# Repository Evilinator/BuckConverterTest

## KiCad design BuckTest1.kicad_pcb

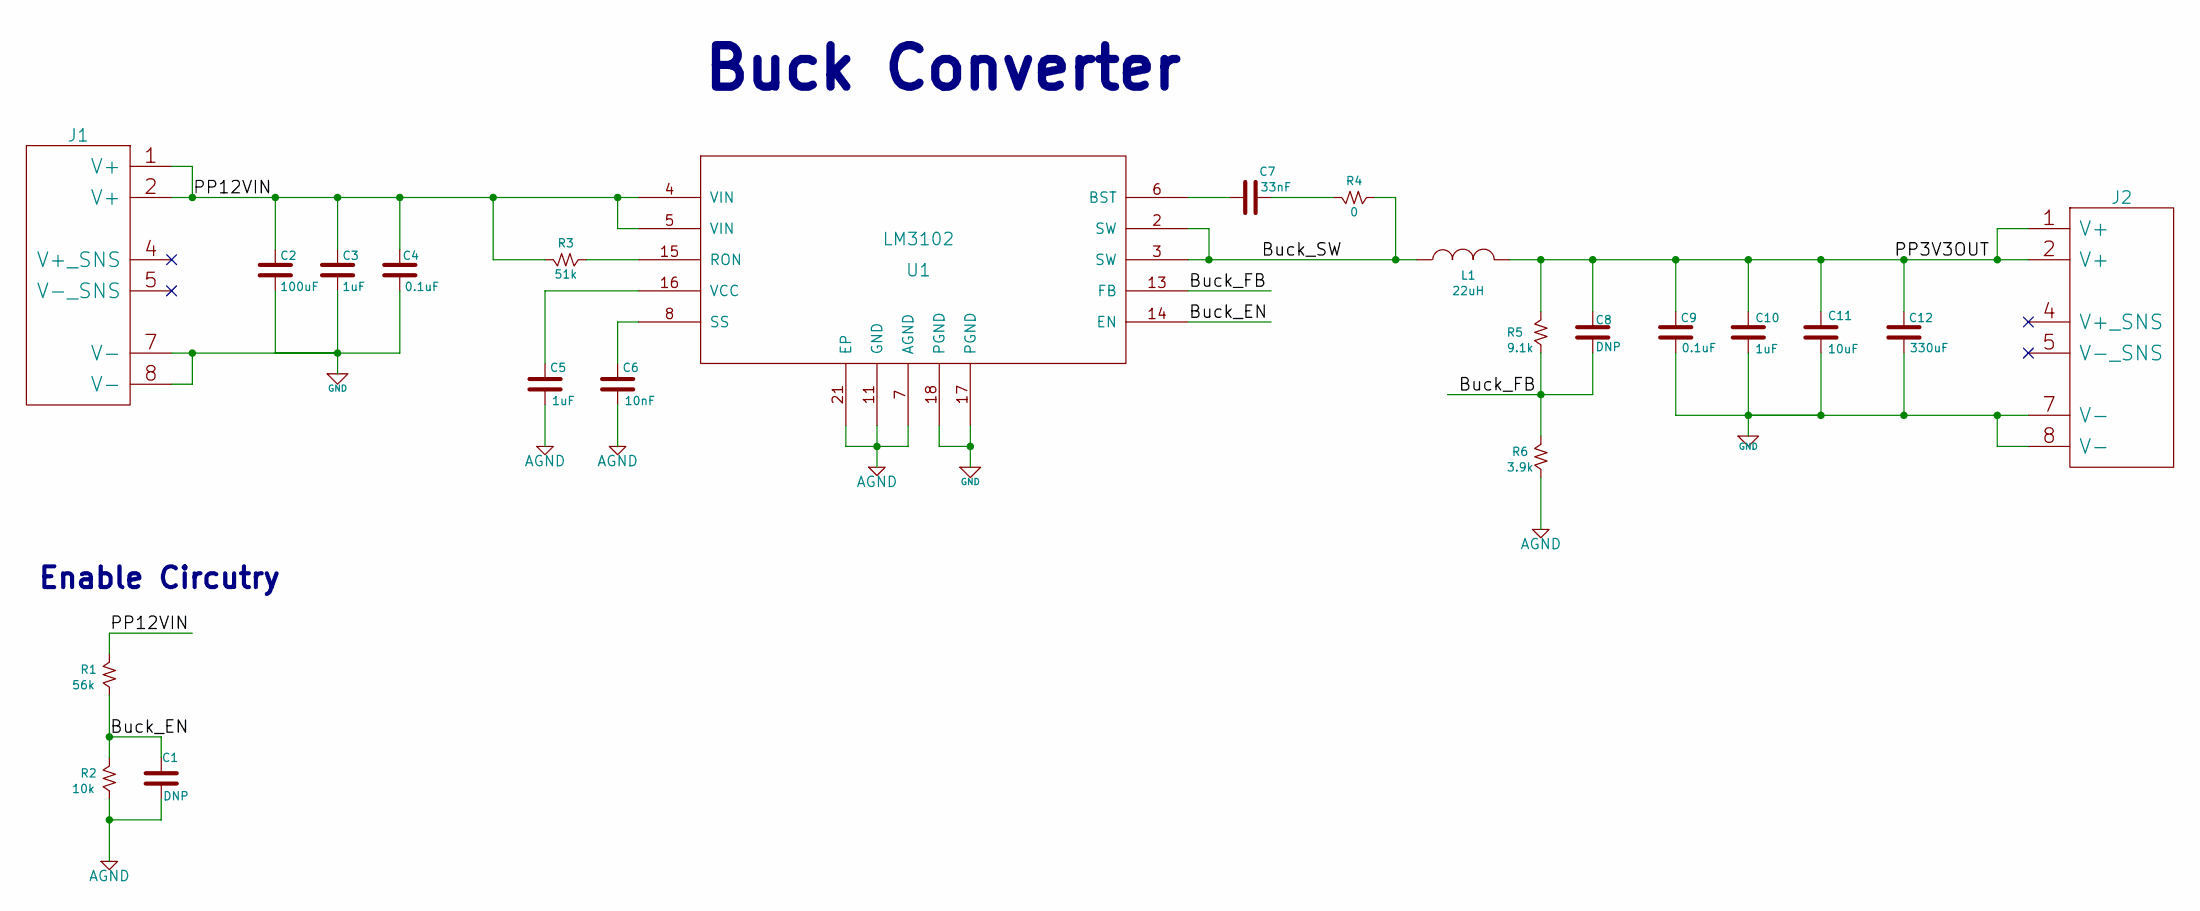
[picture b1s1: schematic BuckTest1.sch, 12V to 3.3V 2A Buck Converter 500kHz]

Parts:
C1, C8: DNP; 0603
C2: 100uF; D3L
C3: 1uF; 0603; Voltage 25V
C4: 0.1uF; 0603; Voltage 25V
C5, C10: 1uF; 0603
C6: 10nF; 0603
C7: 33nF; 0603
C9: 0.1uF; 0603
C11: 10uF; 0603
C12: 330uF; D4
J1, J2: POWERCONN; 8x1 Pin Array
L1: 22uH; SRR1280
R1: 56k; 0603
R2: 10k; 0603
R3: 51k; 0603
R4: 0; 0603
R5: 9.1k; 0603
R6: 3.9k; 0603
U1: LM3102; HTSSOP

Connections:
/Buck_EN: C1.1, R1.2, R2.1, U1.14 (EN)
/Buck_FB: C8.2, R5.2, R6.1, U1.13 (FB)
/Buck_SW: L1.1, R4.2, U1.2 (SW), U1.3 (SW)
/PP3V3OUT: C8.1, C9.1, C10.1, C11.1, C12.1, J2.1 (V+), J2.2 (V+), L1.2, R5.1
/PP12VIN: C2.1, C3.1, C4.1, J1.1 (V+), J1.2 (V+), R1.1, R3.1, U1.4 (VIN), U1.5 (VIN)
AGND: C1.2, C5.2, C6.2, R2.2, R6.2, U1.7 (AGND), U1.11 (GND), U1.21 (EP); also elsewhere on the board
GND: C2.2, C3.2, C4.2, C9.2, C10.2, C11.2, C12.2, J1.7 (V-), J1.8 (V-), J2.7 (V-), J2.8 (V-), U1.17 (PGND), U1.18 (PGND); also elsewhere on the board
unnamed: C7.2, R4.1
unnamed: C5.1, U1.16 (VCC)
unnamed: C6.1, U1.8 (SS)
unnamed: C7.1, U1.6 (BST)
unnamed: R3.2, U1.15 (RON)

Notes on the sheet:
Buck Converter
Enable Circutry

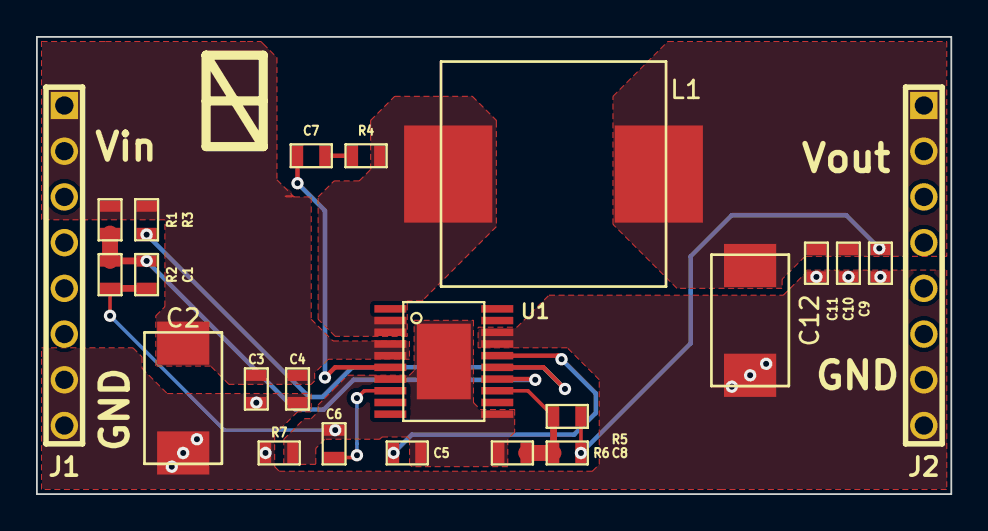
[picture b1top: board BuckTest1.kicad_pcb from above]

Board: 2 copper layers, 50.8 x 25.4 mm, 23 parts (0 on the bottom side), 12 nets.

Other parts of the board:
R7: 0; SM0603

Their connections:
AGND: R7.1; also elsewhere on the board
GND: R7.2; also elsewhere on the board

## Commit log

2013-08-20 Create Repository
    First Creation of the Repository
2013-08-21 Create BOM + Update Component Values
    Need to select new inductor due to non-stock at digikey
    BOM created
    Sch Values Updated
2013-08-21 Added Notice
    Added notice that this design is in progress and not ready for use
2013-08-21 Finalized Component / Footprint Selection
    Schematic and preliminary BOM complete. Layout is next step.
2013-08-23 Created PCB
    Altered schematic to connect GND planes.
    Created layout, single layer implementation not possible
2013-08-27 Copper layout complete
    Hand routed first board to test KiCad layout features. .dsn an .ses are
    autoroute files. Initial copper layout complete, could use improvements
    but will function.
2013-09-16 BuckConverterTest V0
    Silkscreen complete
    Sent for fab to OSH Park
